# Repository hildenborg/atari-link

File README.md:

## About
The purpose of Atari-Link is to give developers using [m68k-atari-dev toolchain](https://github.com/hildenborg/m68k-atari-dev) the possibillity of developing for real Atari computers the same way they are used to target the Hatari emulator.  
If you aren't a developer and only want a ACSI SD-Card hard disk emulator, then there are many other options with better support.  
The [wiki](https://github.com/hildenborg/atari-link/wiki) is recommended for deeper information  

## Hardware
The hardware is designed in KiCad and the project can be found in the "kicad" directory.  
It is designed to be "easy" to build by hand, and the wiki have more information about that.

## Firmware
The hardware is based around the Raspberry Pico and the formware source is in the "firmware" directory.  
The project is dependent on a submodule, so do not forget to do `git submodule init` and `git submodule update` after cloning this git repository.  

## SCSI variant
There is also a design for the SCSI port of the Atari TT, in the "kicad_scsi" directory, built around an RP2350B. It is not yet built or tested; see the [wiki page](https://github.com/hildenborg/atari-link/wiki/ScsiVariant).  
The firmware for it is built from the same source with `cmake -B build_scsi -DATARI_LINK_VARIANT=SCSI`.

## Setup
If you have built the hardware, and just want to get going, then download [atari-link.zip](https://github.com/hildenborg/atari-link/releases/download/Release2/atari_link.zip) and extract its contents.  
Flash the Pico with "atari_link.uf2" and put "config.txt, "tos32mb_ahdi5_boot.img" and "tos32mb_gdbsrv.img" on a FAT32 formatted SD-card.  
This will set you up with a development system that should work on pretty much anything Atari have made.  
You may need to edit the "config.txt" file if you have other hard drives connected, so there aren't any device id collision.  
The hard disk images in the release is TOS 32MB formatted images so they should work on just about anything.  
The "config.txt" in the release is set up so the "tos32mb_ahdi5_boot.img" disk image is not seen by the PC and the "tos32mb_gdbsrv.img" is read-only by the Atari. The "tos32mb_gdbsrv.img" is visible on the PC as a USB drive and files written to it are immediately accessible on the Atari.  
NOTE: Even TOS formatted hard disk images are accessible to the PC as a USB drive. There's a [wiki page](https://github.com/hildenborg/atari-link/wiki/ProblemsSolutions) that describes how it works.

## Usage
The "extras" directory contains a "hello world" example using VsCode and Atari-Link with m68k-atari-dev toolchain.  
This example works exactly the same as the "vscode_hatari" example in the m68k-atari-dev examples.  
After having set up your Atari-Link with firmware and a SD-Card with the released images, you should now be able to start your atari and have a C and D drive (you may have to install the D drive).  
The D drive is the drive that appears as a USB drive on your PC. This is specified in the "config.txt" file that came with the disk images.  
On the D drive there is "gdbsrv.ttp" which you start with "--multi hello.prg" arguments.  
On your PC, execute "./vscode.sh" and in VsCode, press "Shoft-Ctrl-B" to build and "F5" to execute on your atari.  

## License:
This project is MIT licensed.  
The submodule: [no-OS-FatFS-SD-SPI-RPi-Pico](https://github.com/carlk3/no-OS-FatFS-SD-SPI-RPi-Pico) is a separate project and is Apache-2.0 licensed.

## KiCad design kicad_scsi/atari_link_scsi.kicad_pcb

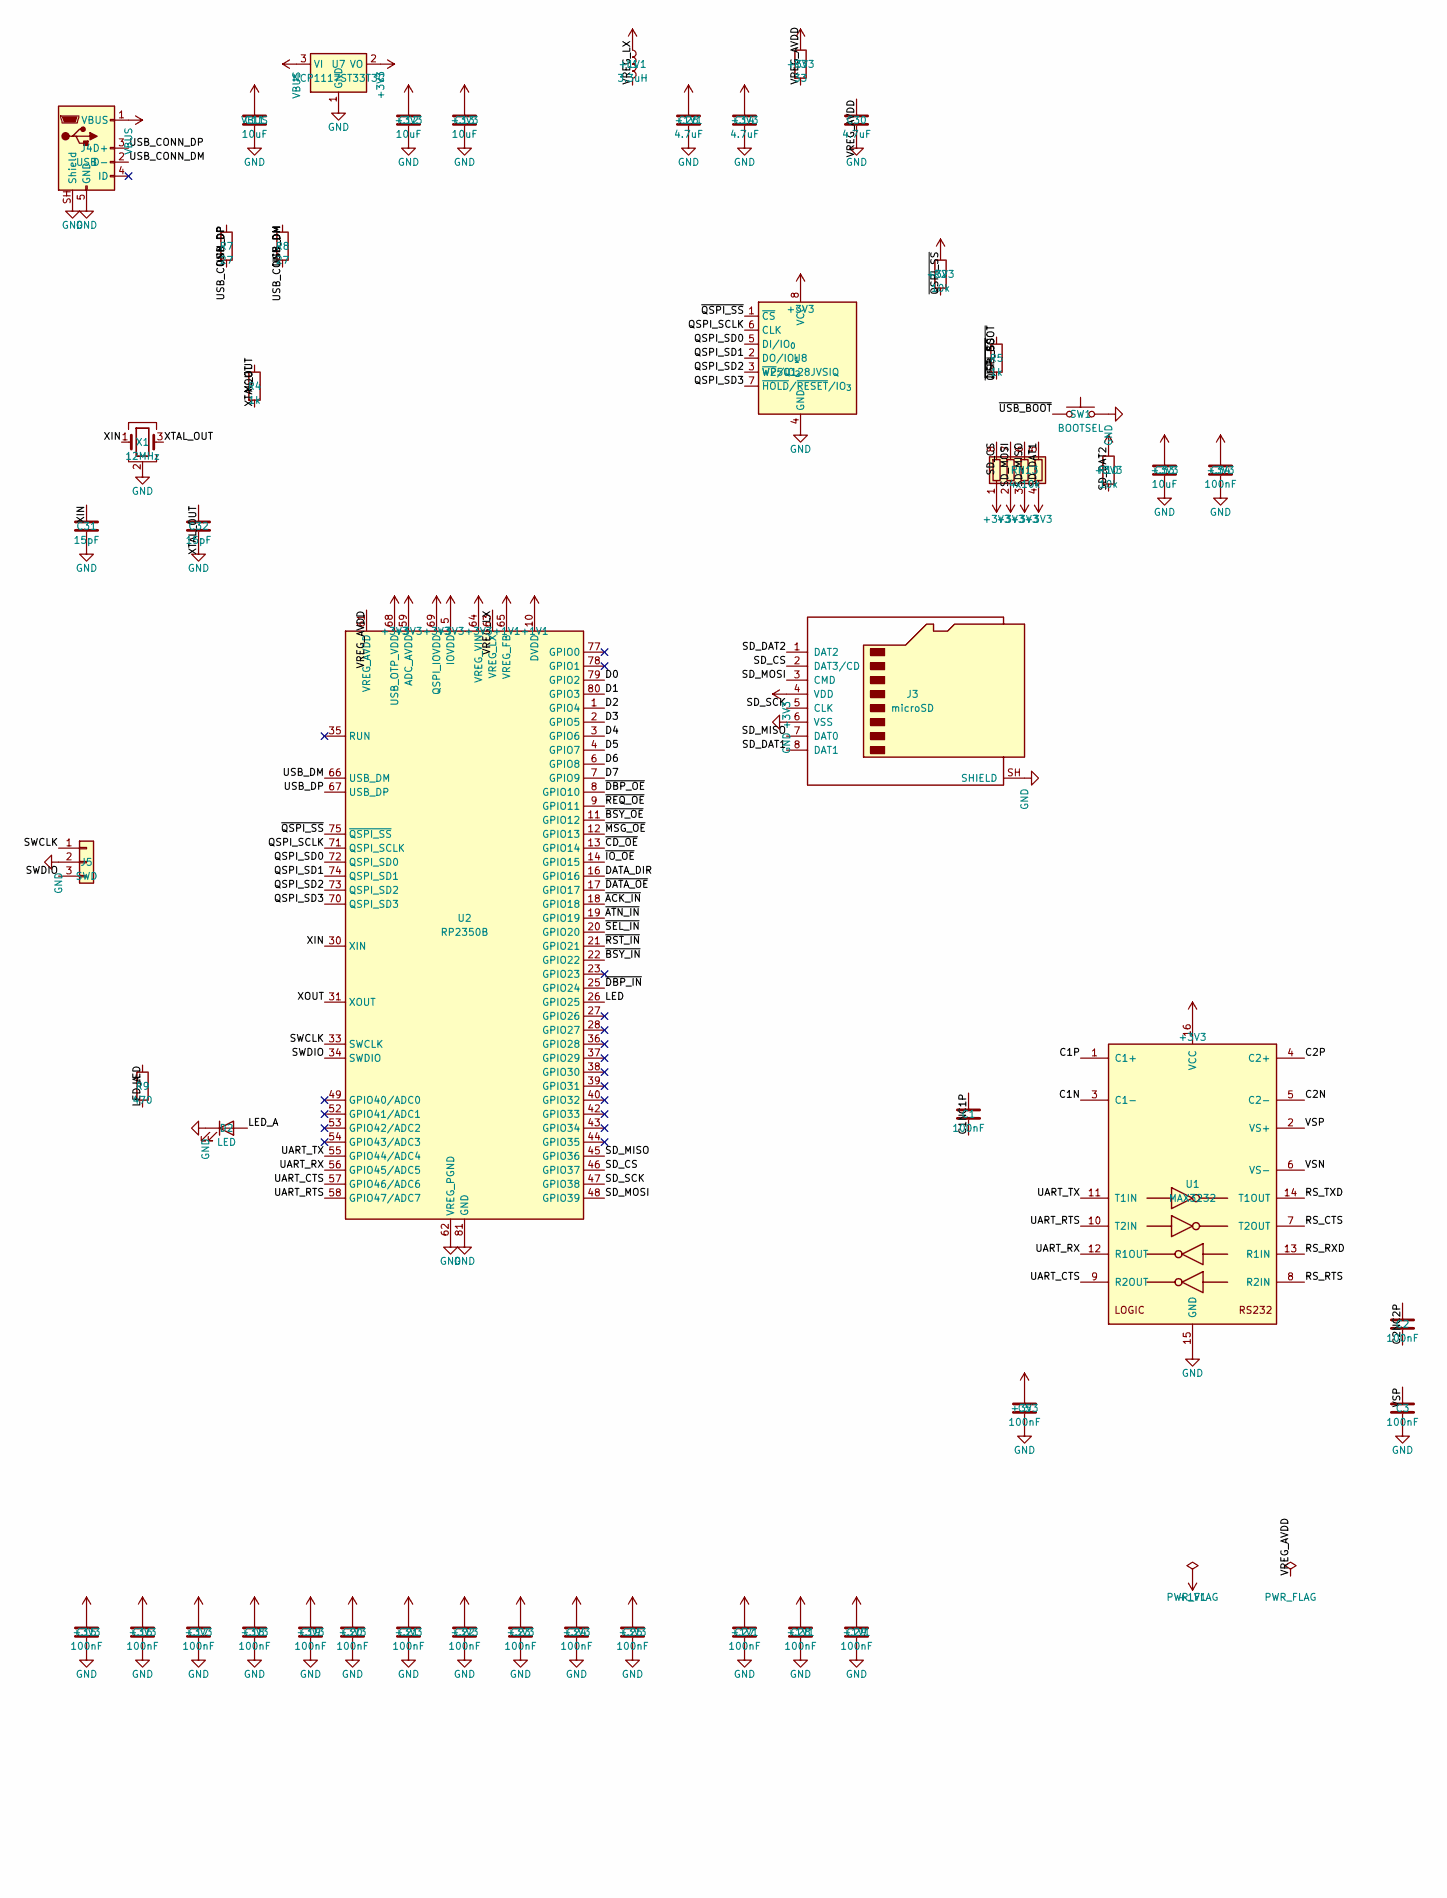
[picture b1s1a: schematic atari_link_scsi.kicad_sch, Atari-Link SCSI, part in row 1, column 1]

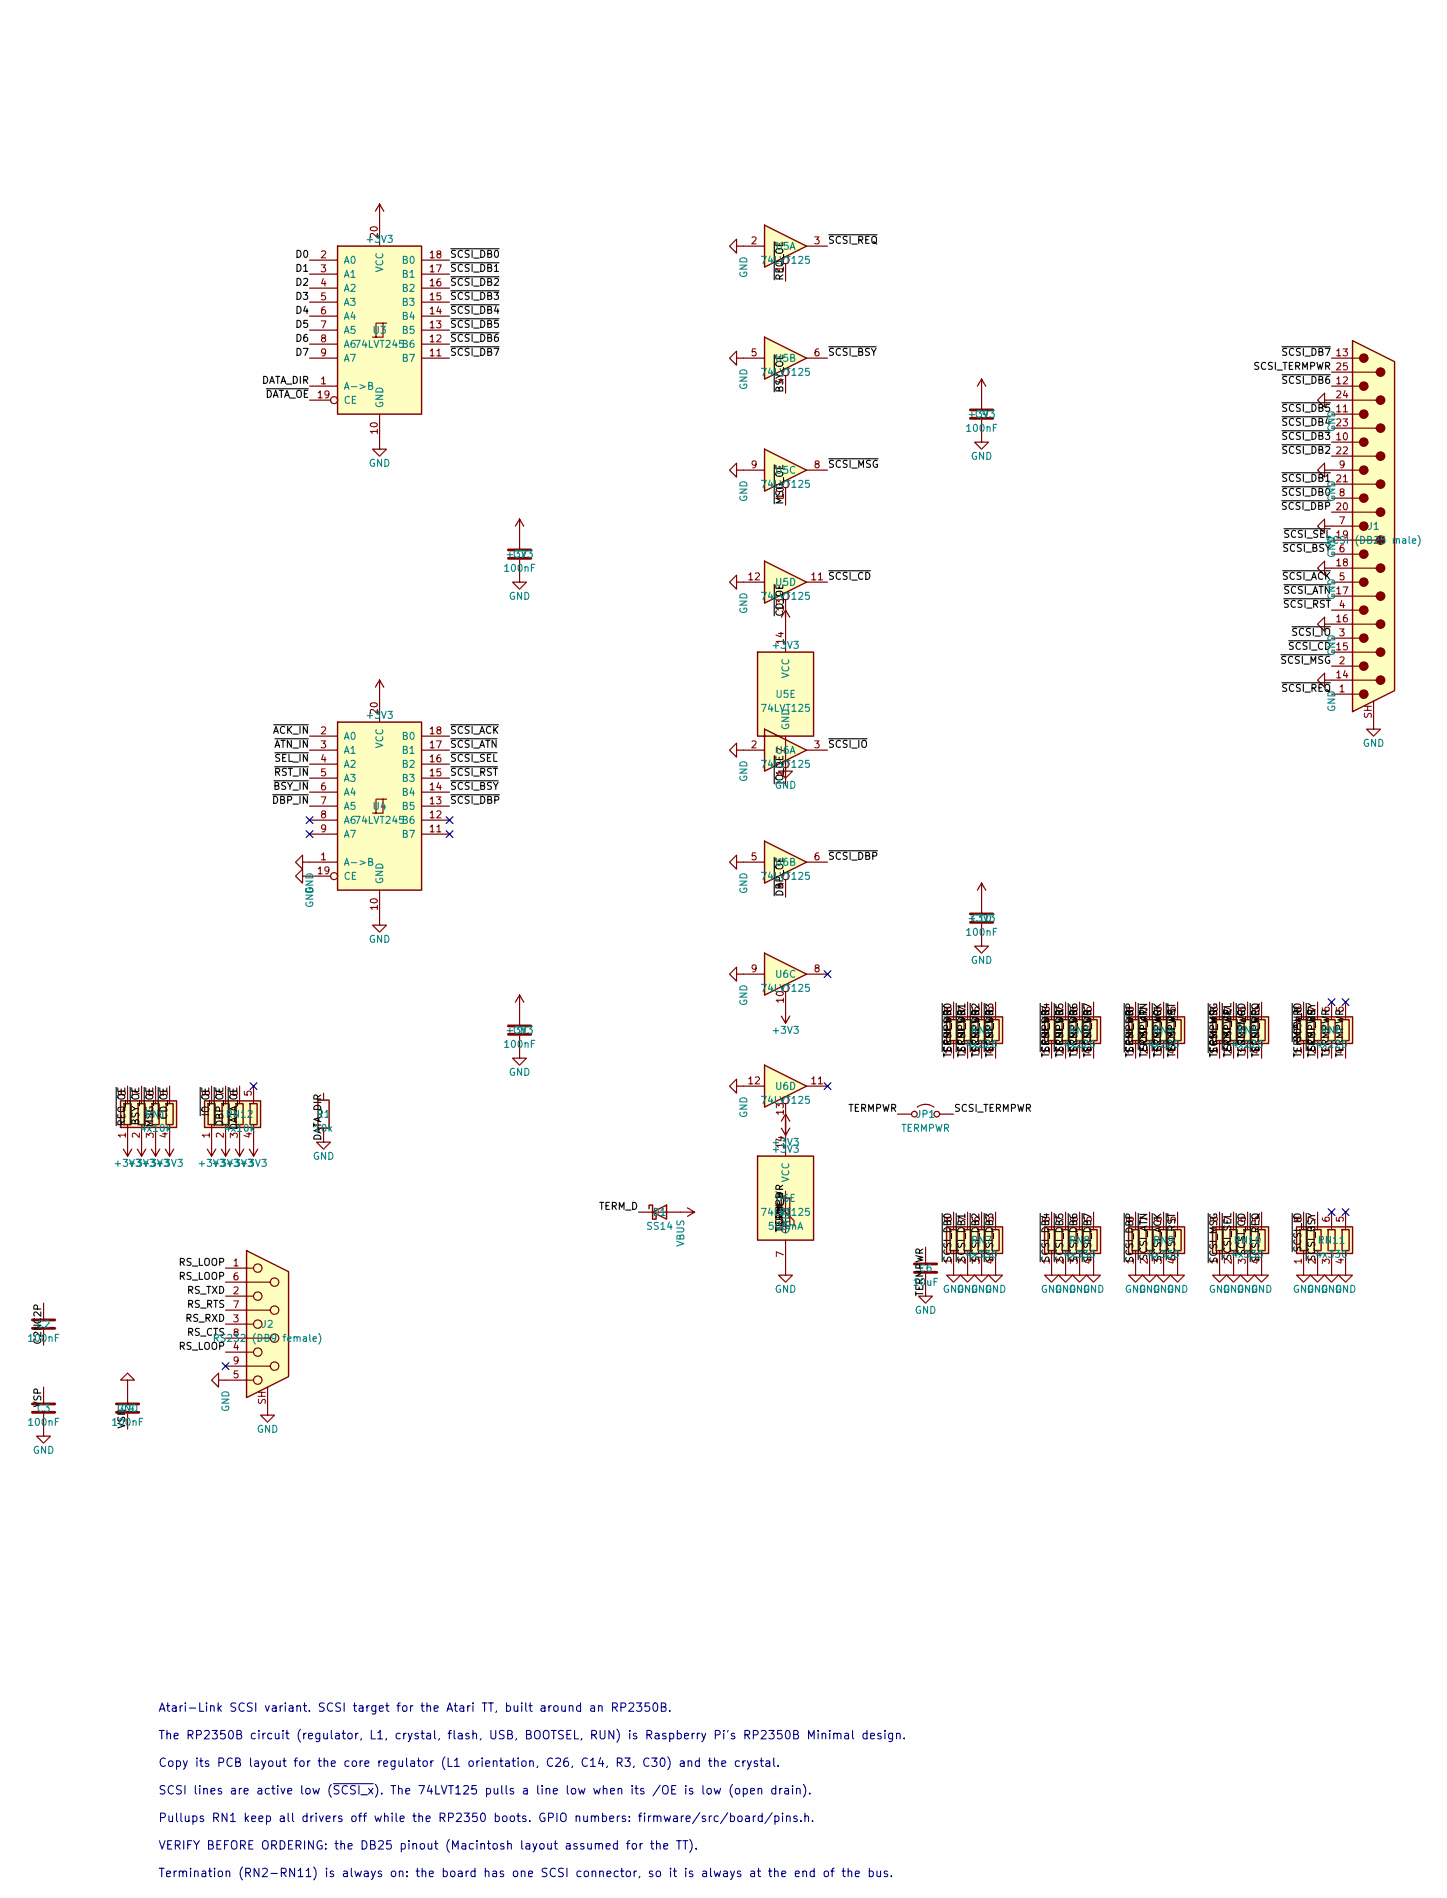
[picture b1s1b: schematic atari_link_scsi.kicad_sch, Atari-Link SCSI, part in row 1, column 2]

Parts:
C1, C2, C3, C4, C5, C7, C8, C9, C10, C34: 100nF; C_0603_1608Metric
C6, C11, C12, C13, C33: 10uF; C_0805_2012Metric
C14, C26, C30: 4.7uF; C_0402_1005Metric
C15, C16, C17, C18, C19, C20, C21, C22, C23, C24, C25, C27, C28, C29: 100nF; C_0402_1005Metric
C31, C32: 15pF; C_0402_1005Metric
D1: SS14; D_SMA
D2: LED; LED_0603_1608Metric
F1: 500mA; Fuse_1812_4532Metric
J1: SCSI (DB25 male); DSUB-25_Pins_Horizontal_P2.77x2.84mm_EdgePinOffset9.90mm_Ho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
J2: RS232 (DB9 female); DSUB-9_Socket_Horizontal_P2.77x2.84mm_EdgePinOffset9.90mm_H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
J3: microSD; microSD_HC_Wuerth_693072010801
J4: USB; USB_Micro-B_Amphenol_10103594-0001LF_Horizontal
J5: SWD; PinHeader_1x03_P2.54mm_Vertical
JP1: TERMPWR; PinHeader_1x02_P2.54mm_Vertical
L1: 3.3uH; L_Abracon_AOTA-B201610S
R1, R10: 10k; R_0603_1608Metric
R2: 10k; R_0402_1005Metric
R3: 33; R_0402_1005Metric
R4, R5: 1k; R_0402_1005Metric
R7, R8: 27; R_0402_1005Metric
R9: 470; R_0402_1005Metric
RN1, RN12, RN13: 4x10k; R_Array_Convex_4x0603
RN2, RN3, RN4, RN5, RN6: 4x220; R_Array_Convex_4x0603
RN7, RN8, RN9, RN10, RN11: 4x330; R_Array_Convex_4x0603
SW1: BOOTSEL; SW_Push_1P1T_NO_Vertical_Wuerth_434133025816
U1: MAX3232; SOIC-16_3.9x9.9mm_P1.27mm
U2: RP2350B; QFN-80-1EP_10x10mm_P0.4mm_EP3.4x3.4mm_ThermalVias
U3, U4: 74LVT245; SOIC-20W_7.5x12.8mm_P1.27mm
U5, U6: 74LVT125; SOIC-14_3.9x8.7mm_P1.27mm
U7: NCP1117ST33T3G; SOT-223-3_TabPin2
U8: W25Q128JVSIQ; SOIC-8_5.3x5.3mm_P1.27mm
X1: 12MHz; Crystal_SMD_3225-4Pin_3.2x2.5mm

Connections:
+1V1: C26.1, C27.1, C28.1, C29.1, L1.1, U2.10 (DVDD), U2.32 (DVDD), U2.51 (DVDD), U2.65 (VREG_FB)
+3V3: C5.1, C7.1, C8.1, C9.1, C10.1, C12.1, C13.1, C14.1, C15.1, C16.1, C17.1, C18.1, C19.1, C20.1, C21.1, C22.1, C23.1, C24.1, C25.1, C33.1, C34.1, J3.4 (VDD), R2.1, R3.1, R10.1, RN1.1 (R1.1), RN1.2 (R2.1), RN1.3 (R3.1), RN1.4 (R4.1), RN12.1 (R1.1), RN12.2 (R2.1), RN12.3 (R3.1), RN12.4 (R4.1), RN13.1 (R1.1), RN13.2 (R2.1), RN13.3 (R3.1), RN13.4 (R4.1), U1.16 (VCC), U2.5 (IOVDD), U2.15 (IOVDD), U2.24 (IOVDD), U2.29 (IOVDD), U2.41 (IOVDD), U2.50 (IOVDD), U2.59 (ADC_AVDD), U2.60 (IOVDD), U2.64 (VREG_VIN), U2.68 (USB_OTP_VDD), U2.69 (QSPI_IOVDD), U2.76 (IOVDD), U3.20 (VCC), U4.20 (VCC), U5.14 (VCC), U6.10, U6.13, U6.14 (VCC), U7.2 (VO), U8.8 (VCC)
/C1N: C1.2, U1.3 (C1-)
/C1P: C1.1, U1.1 (C1+)
/C2N: C2.2, U1.5 (C2-)
/C2P: C2.1, U1.4 (C2+)
/D0: U2.79 (GPIO2), U3.2 (A0)
/D1: U2.80 (GPIO3), U3.3 (A1)
/D2: U2.1 (GPIO4), U3.4 (A2)
/D3: U2.2 (GPIO5), U3.5 (A3)
/D4: U2.3 (GPIO6), U3.6 (A4)
/D5: U2.4 (GPIO7), U3.7 (A5)
/D6: U2.6 (GPIO8), U3.8 (A6)
/D7: U2.7 (GPIO9), U3.9 (A7)
/DATA_DIR: R1.1, U2.16 (GPIO16), U3.1 (A->B)
/LED: R9.1, U2.26 (GPIO25)
/LED_A: D2.2 (A), R9.2
/QSPI_SCLK: U2.71 (QSPI_SCLK), U8.6 (CLK)
/QSPI_SD0: U2.72 (QSPI_SD0), U8.5 (DI/IO_{0})
/QSPI_SD1: U2.74 (QSPI_SD1), U8.2 (DO/IO_{1})
/QSPI_SD2: U2.73 (QSPI_SD2), U8.3 (~WP/IO_{2})
/QSPI_SD3: U2.70 (QSPI_SD3), U8.7 (~HOLD/~RESET/IO_{3})
/RS_CTS: J2.8, U1.7 (T2OUT)
/RS_LOOP: J2.1, J2.4, J2.6
/RS_RTS: J2.7, U1.8 (R2IN)
/RS_RXD: J2.3, U1.13 (R1IN)
/RS_TXD: J2.2, U1.14 (T1OUT)
/SCSI_TERMPWR: J1.25, JP1.2 (B)
/SD_CS: J3.2 (DAT3/CD), RN13.8 (R1.2), U2.46 (GPIO37)
/SD_DAT1: J3.8 (DAT1), RN13.5 (R4.2)
/SD_DAT2: J3.1 (DAT2), R10.2
/SD_MISO: J3.7 (DAT0), RN13.6 (R3.2), U2.45 (GPIO36)
/SD_MOSI: J3.3 (CMD), RN13.7 (R2.2), U2.48 (GPIO39)
/SD_SCK: J3.5 (CLK), U2.47 (GPIO38)
/SWCLK: J5.1, U2.33 (SWCLK)
/SWDIO: J5.3, U2.34 (SWDIO)
/TERMPWR: C6.1, F1.2, JP1.1 (A), RN2.1 (R1.1), RN2.2 (R2.1), RN2.3 (R3.1), RN2.4 (R4.1), RN3.1 (R1.1), RN3.2 (R2.1), RN3.3 (R3.1), RN3.4 (R4.1), RN4.1 (R1.1), RN4.2 (R2.1), RN4.3 (R3.1), RN4.4 (R4.1), RN5.1 (R1.1), RN5.2 (R2.1), RN5.3 (R3.1), RN5.4 (R4.1), RN6.1 (R1.1), RN6.2 (R2.1), RN6.3 (R3.1), RN6.4 (R4.1)
/TERM_D: D1.1 (K), F1.1
/UART_CTS: U1.9 (R2OUT), U2.57 (GPIO46/ADC6)
/UART_RTS: U1.10 (T2IN), U2.58 (GPIO47/ADC7)
/UART_RX: U1.12 (R1OUT), U2.56 (GPIO45/ADC5)
/UART_TX: U1.11 (T1IN), U2.55 (GPIO44/ADC4)
/USB_CONN_DM: J4.2 (D-), R8.1
/USB_CONN_DP: J4.3 (D+), R7.1
/USB_DM: R8.2, U2.66 (USB_DM)
/USB_DP: R7.2, U2.67 (USB_DP)
/VREG_AVDD: C30.1, R3.2, U2.61 (VREG_AVDD)
/VREG_LX: L1.2, U2.63 (VREG_LX)
/VSN: C4.2, U1.6 (VS-)
/VSP: C3.1, U1.2 (VS+)
/XIN: C31.1, U2.30 (XIN), X1.1
/XOUT: R4.1, U2.31 (XOUT)
/XTAL_OUT: C32.1, R4.2, X1.3
/~ACK_IN: U2.18 (GPIO18), U4.2 (A0)
/~ATN_IN: U2.19 (GPIO19), U4.3 (A1)
/~BSY_IN: U2.22 (GPIO22), U4.6 (A4)
/~BSY_OE: RN1.7 (R2.2), U2.11 (GPIO12), U5.4
/~CD_OE: RN1.5 (R4.2), U2.13 (GPIO14), U5.13
/~DATA_OE: RN12.6 (R3.2), U2.17 (GPIO17), U3.19 (CE)
/~DBP_IN: U2.25 (GPIO24), U4.7 (A5)
/~DBP_OE: RN12.7 (R2.2), U2.8 (GPIO10), U6.4
/~IO_OE: RN12.8 (R1.2), U2.14 (GPIO15), U6.1
/~MSG_OE: RN1.6 (R3.2), U2.12 (GPIO13), U5.10
/~QSPI_SS: R2.2, R5.1, U2.75 (~QSPI_SS), U8.1 (~CS)
/~REQ_OE: RN1.8 (R1.2), U2.9 (GPIO11), U5.1
/~RST_IN: U2.21 (GPIO21), U4.5 (A3)
/~SCSI_ACK: J1.5, RN4.6 (R3.2), RN9.6 (R3.2), U4.18 (B0)
/~SCSI_ATN: J1.17, RN4.7 (R2.2), RN9.7 (R2.2), U4.17 (B1)
/~SCSI_BSY: J1.6, RN6.7 (R2.2), RN11.7 (R2.2), U4.14 (B4), U5.6
/~SCSI_CD: J1.15, RN5.6 (R3.2), RN10.6 (R3.2), U5.11
/~SCSI_DB0: J1.8, RN2.8 (R1.2), RN7.8 (R1.2), U3.18 (B0)
/~SCSI_DB1: J1.21, RN2.7 (R2.2), RN7.7 (R2.2), U3.17 (B1)
/~SCSI_DB2: J1.22, RN2.6 (R3.2), RN7.6 (R3.2), U3.16 (B2)
/~SCSI_DB3: J1.10, RN2.5 (R4.2), RN7.5 (R4.2), U3.15 (B3)
/~SCSI_DB4: J1.23, RN3.8 (R1.2), RN8.8 (R1.2), U3.14 (B4)
/~SCSI_DB5: J1.11, RN3.7 (R2.2), RN8.7 (R2.2), U3.13 (B5)
/~SCSI_DB6: J1.12, RN3.6 (R3.2), RN8.6 (R3.2), U3.12 (B6)
/~SCSI_DB7: J1.13, RN3.5 (R4.2), RN8.5 (R4.2), U3.11 (B7)
/~SCSI_DBP: J1.20, RN4.8 (R1.2), RN9.8 (R1.2), U4.13 (B5), U6.6
/~SCSI_IO: J1.3, RN6.8 (R1.2), RN11.8 (R1.2), U6.3
/~SCSI_MSG: J1.2, RN5.8 (R1.2), RN10.8 (R1.2), U5.8
/~SCSI_REQ: J1.1, RN5.5 (R4.2), RN10.5 (R4.2), U5.3
/~SCSI_RST: J1.4, RN4.5 (R4.2), RN9.5 (R4.2), U4.15 (B3)
/~SCSI_SEL: J1.19, RN5.7 (R2.2), RN10.7 (R2.2), U4.16 (B2)
/~SEL_IN: U2.20 (GPIO20), U4.4 (A2)
/~USB_BOOT: R5.2, SW1.1
GND: C3.2, C4.1, C5.2, C6.2, C7.2, C8.2, C9.2, C10.2, C11.2, C12.2, C13.2, C14.2, C15.2, C16.2, C17.2, C18.2, C19.2, C20.2, C21.2, C22.2, C23.2, C24.2, C25.2, C26.2, C27.2, C28.2, C29.2, C30.2, C31.2, C32.2, C33.2, C34.2, D2.1 (K), J1.7, J1.9, J1.14, J1.16, J1.18, J1.24, J1.SH (PAD), J2.5, J2.SH (PAD), J3.6 (VSS), J3.SH (SHIELD), J4.5 (GND), J4.SH (Shield), J5.2, R1.2, RN7.1 (R1.1), RN7.2 (R2.1), RN7.3 (R3.1), RN7.4 (R4.1), RN8.1 (R1.1), RN8.2 (R2.1), RN8.3 (R3.1), RN8.4 (R4.1), RN9.1 (R1.1), RN9.2 (R2.1), RN9.3 (R3.1), RN9.4 (R4.1), RN10.1 (R1.1), RN10.2 (R2.1), RN10.3 (R3.1), RN10.4 (R4.1), RN11.1 (R1.1), RN11.2 (R2.1), RN11.3 (R3.1), RN11.4 (R4.1), SW1.2, U1.15 (GND), U2.62 (VREG_PGND), U2.81 (GND), U3.10 (GND), U4.1 (A->B), U4.10 (GND), U4.19 (CE), U5.2, U5.5, U5.7 (GND), U5.9, U5.12, U6.2, U6.5, U6.7 (GND), U6.9, U6.12, U7.1 (GND), U8.4 (GND), X1.2 (G), X1.4 (G)
VBUS: C11.1, D1.2 (A), J4.1 (VBUS), U7.3 (VI)

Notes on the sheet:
Pullups RN1 keep all drivers off while the RP2350 boots. GPIO numbers: firmware/src/board/pins.h.
Termination (RN2-RN11) is always on: the board has one SCSI connector, so it is always at the end of the bus.
Copy its PCB layout for the core regulator (L1 orientation, C26, C14, R3, C30) and the crystal.
Atari-Link SCSI variant. SCSI target for the Atari TT, built around an RP2350B.
SCSI lines are active low (~{SCSI_x}). The 74LVT125 pulls a line low when its /OE is low (open drain).
VERIFY BEFORE ORDERING: the DB25 pinout (Macintosh layout assumed for the TT).
The RP2350B circuit (regulator, L1, crystal, flash, USB, BOOTSEL, RUN) is Raspberry Pi's RP2350B Minimal design.

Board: 2 copper layers, 76 parts (0 on the bottom side), 88 nets, no tracks yet.

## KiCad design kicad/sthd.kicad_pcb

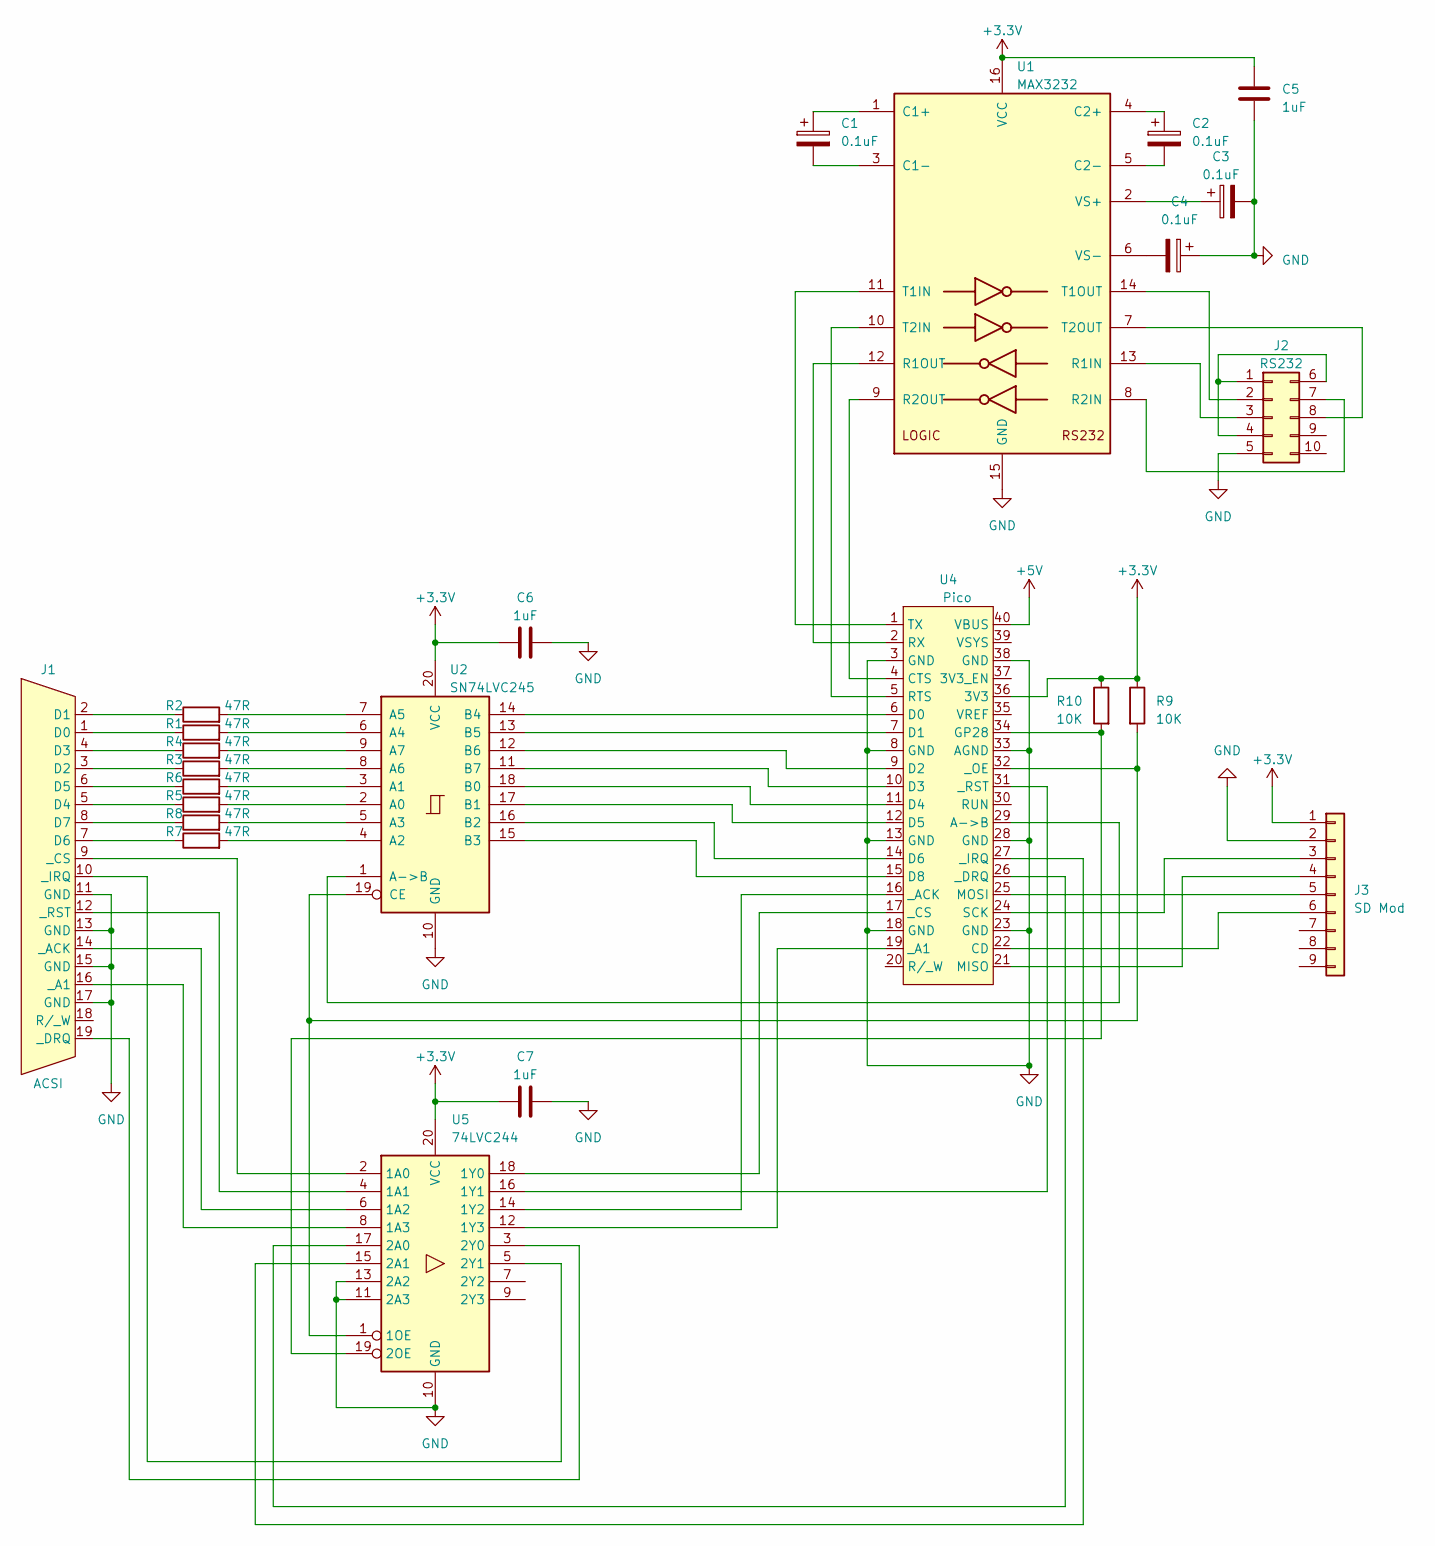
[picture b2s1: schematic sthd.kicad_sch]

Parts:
C1, C2, C3, C4: 0.1uF; CP_Radial_D5.0mm_P2.00mm
C5, C6, C7: 1uF; C_Disc_D5.0mm_W2.5mm_P5.00mm
J1: ACSI; DB19
J2: RS232; IDC-Header_2x05_P2.54mm_Vertical
J3: SD Mod; PinHeader_1x09_P2.54mm_Vertical
R1, R2, R3, R4, R5, R6, R7, R8: 47R; R_Axial_DIN0207_L6.3mm_D2.5mm_P10.16mm_Horizontal
R9, R10: 10K; R_Axial_DIN0207_L6.3mm_D2.5mm_P10.16mm_Horizontal
U1: MAX3232; DIP-16_W7.62mm
U2: SN74LVC245; DIP-20_W7.62mm
U4: Pico
U5: 74LVC244; DIP-20_W7.62mm

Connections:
+3.3V: C5.1, C6.1, C7.1, J3.1, R9.1, R10.1, U1.16 (VCC), U2.20 (VCC), U4.36 (3V3), U5.20 (VCC)
+5V: U4.40 (VBUS)
GND: C3.2, C4.1, C5.2, C6.2, C7.2, J1.11 (GND), J1.13 (GND), J1.15 (GND), J1.17 (GND), J2.5, J3.2, U1.15 (GND), U2.10 (GND), U4.3 (GND), U4.8 (GND), U4.13 (GND), U4.18 (GND), U4.23 (GND), U4.28 (GND), U4.33 (AGND), U4.38 (GND), U5.10 (GND), U5.11 (2A3), U5.13 (2A2)
unnamed: J1.1 (D0), R1.1
unnamed: J1.2 (D1), R2.1
unnamed: J1.3 (D2), R3.1
unnamed: J1.4 (D3), R4.1
unnamed: J1.5 (D4), R5.1
unnamed: J1.6 (D5), R6.1
unnamed: J1.7 (D6), R7.1
unnamed: J1.8 (D7), R8.1
unnamed: J1.16 (_A1), U5.8 (1A3)
unnamed: J1.14 (_ACK), U5.6 (1A2)
unnamed: J1.9 (_CS), U5.2 (1A0)
unnamed: J1.19 (_DRQ), U5.3 (2Y0)
unnamed: J1.10 (_IRQ), U5.5 (2Y1)
unnamed: J1.12 (_RST), U5.4 (1A1)
unnamed: J2.1, J2.4, J2.6
unnamed: J2.2, U1.14 (T1OUT)
unnamed: J2.3, U1.13 (R1IN)
unnamed: J2.7, U1.8 (R2IN)
unnamed: J2.8, U1.7 (T2OUT)
unnamed: J3.3, U4.24 (SCK)
unnamed: J3.4, U4.21 (MISO)
unnamed: J3.5, U4.25 (MOSI)
unnamed: J3.6, U4.22 (CD)
unnamed: C1.1, U1.1 (C1+)
unnamed: C1.2, U1.3 (C1-)
unnamed: C2.1, U1.4 (C2+)
unnamed: C2.2, U1.5 (C2-)
unnamed: U1.12 (R1OUT), U4.2 (RX)
unnamed: U1.9 (R2OUT), U4.4 (CTS)
unnamed: U1.11 (T1IN), U4.1 (TX)
unnamed: U1.10 (T2IN), U4.5 (RTS)
unnamed: C3.1, U1.2 (VS+)
unnamed: C4.2, U1.6 (VS-)
unnamed: R5.2, U2.2 (A0)
unnamed: R6.2, U2.3 (A1)
unnamed: R7.2, U2.4 (A2)
unnamed: R8.2, U2.5 (A3)
unnamed: R1.2, U2.6 (A4)
unnamed: R2.2, U2.7 (A5)
unnamed: R3.2, U2.8 (A6)
unnamed: R4.2, U2.9 (A7)
unnamed: U2.1 (A->B), U4.29 (A->B)
unnamed: U2.18 (B0), U4.11 (D4)
unnamed: U2.17 (B1), U4.12 (D5)
unnamed: U2.16 (B2), U4.14 (D6)
unnamed: U2.15 (B3), U4.15 (D8)
unnamed: U2.14 (B4), U4.6 (D0)
unnamed: U2.13 (B5), U4.7 (D1)
unnamed: U2.12 (B6), U4.9 (D2)
unnamed: U2.11 (B7), U4.10 (D3)
unnamed: R9.2, U2.19 (CE), U4.32 (_OE), U5.1 (1OE)
unnamed: R10.2, U4.34 (GP28), U5.19 (2OE)
unnamed: U4.19 (_A1), U5.12 (1Y3)
unnamed: U4.16 (_ACK), U5.14 (1Y2)
unnamed: U4.17 (_CS), U5.18 (1Y0)
unnamed: U4.26 (_DRQ), U5.17 (2A0)
unnamed: U4.27 (_IRQ), U5.15 (2A1)
unnamed: U4.31 (_RST), U5.16 (1Y1)

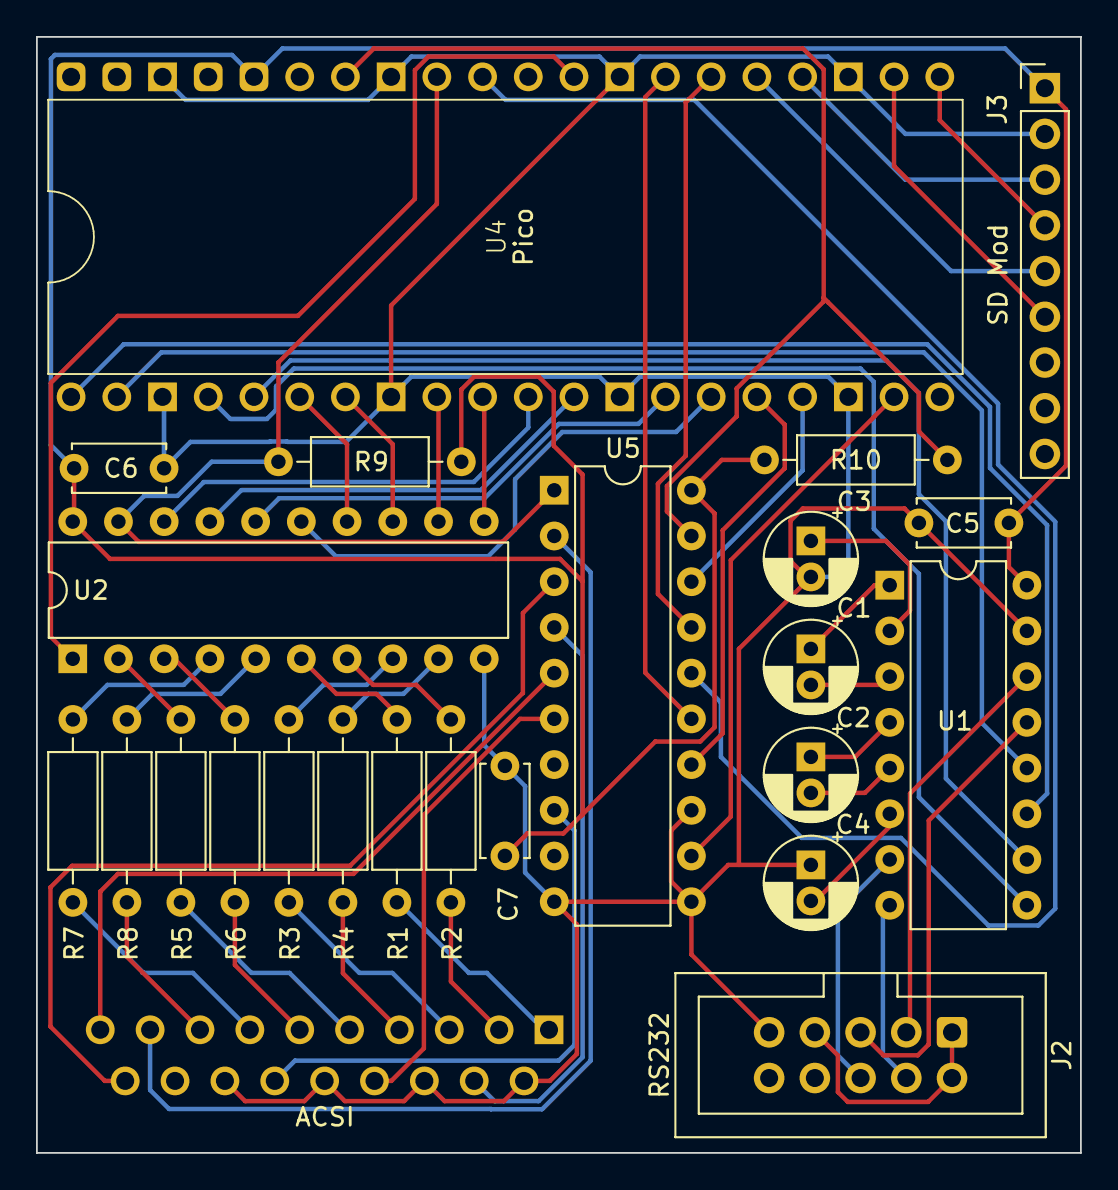
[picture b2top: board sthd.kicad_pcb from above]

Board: 2 copper layers, 58.0 x 62.0 mm, 24 parts (1 on the bottom side), 60 nets.

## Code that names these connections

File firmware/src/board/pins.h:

#ifndef PINS_DEFINED
#define PINS_DEFINED

// GPIO assignments for the two hardware variants.
// ATARI_LINK_SCSI is set by CMake when building the SCSI variant (RP2350B).
// The ACSI port pins are defined in acsi/acsi.cpp and acsi/acsi_asm.pio.

#ifdef ATARI_LINK_SCSI

// RS-232, UART0
#define PIN_UART_TX		44
#define PIN_UART_RX		45
#define PIN_UART_CTS	46
#define PIN_UART_RTS	47

// SD-Card, SPI0
#define PIN_SD_MISO		36
#define PIN_SD_CS		37
#define PIN_SD_SCK		38
#define PIN_SD_MOSI		39

// SCSI bus. All pins used by the PIO must be below 32.
// Data and DBP go through a 74LVT245 (DB0-7) and a 74LVT125 (DBP).
#define PIN_SCSI_DB0		2	// DB0-DB7 are 2-9
#define PIN_SCSI_DBP		10	// 74LVT125 /OE, low asserts DBP
// 74LVT125 /OE, low asserts the bus signal
#define PIN_SCSI_REQ		11
#define PIN_SCSI_BSY_OUT	12
#define PIN_SCSI_MSG		13
#define PIN_SCSI_CD			14
#define PIN_SCSI_IO			15
// Data bus 74LVT245 control
#define PIN_SCSI_DATA_DIR	16	// High: Pico drives the bus. Low: Pico reads the bus.
#define PIN_SCSI_DATA_OE	17	// Low enables the 74LVT245
// Bus inputs through a 74LVT245, low when asserted
#define PIN_SCSI_ACK		18
#define PIN_SCSI_ATN		19
#define PIN_SCSI_SEL		20
#define PIN_SCSI_RST		21
#define PIN_SCSI_BSY_IN		22
#define PIN_SCSI_DBP_IN		24

#else // ACSI variant (RP2040 Pico)

// RS-232, UART0
#define PIN_UART_TX		0
#define PIN_UART_RX		1
#define PIN_UART_CTS	2
#define PIN_UART_RTS	3

// SD-Card, SPI0
#define PIN_SD_MISO		16
#define PIN_SD_CS		17
#define PIN_SD_SCK		18
#define PIN_SD_MOSI		19

#endif

#endif // PINS_DEFINED

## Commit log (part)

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2026-06-04 setting up repo
2026-06-04 redoing submodules
2026-06-04 submodule license
2026-06-04 removed headline
2026-06-07 Updated project settings.
2026-06-10 Correct setting of oe1 and oe2 when startup or reset.
2026-06-10 documenting
2026-06-16 Fixed bug where ACSI emulation randomly would not start after power off and on.
2026-06-19 fixed release link
2026-06-21 hello world
